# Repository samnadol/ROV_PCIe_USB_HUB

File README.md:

# PCIe USB Hub for Pi 5

# Images

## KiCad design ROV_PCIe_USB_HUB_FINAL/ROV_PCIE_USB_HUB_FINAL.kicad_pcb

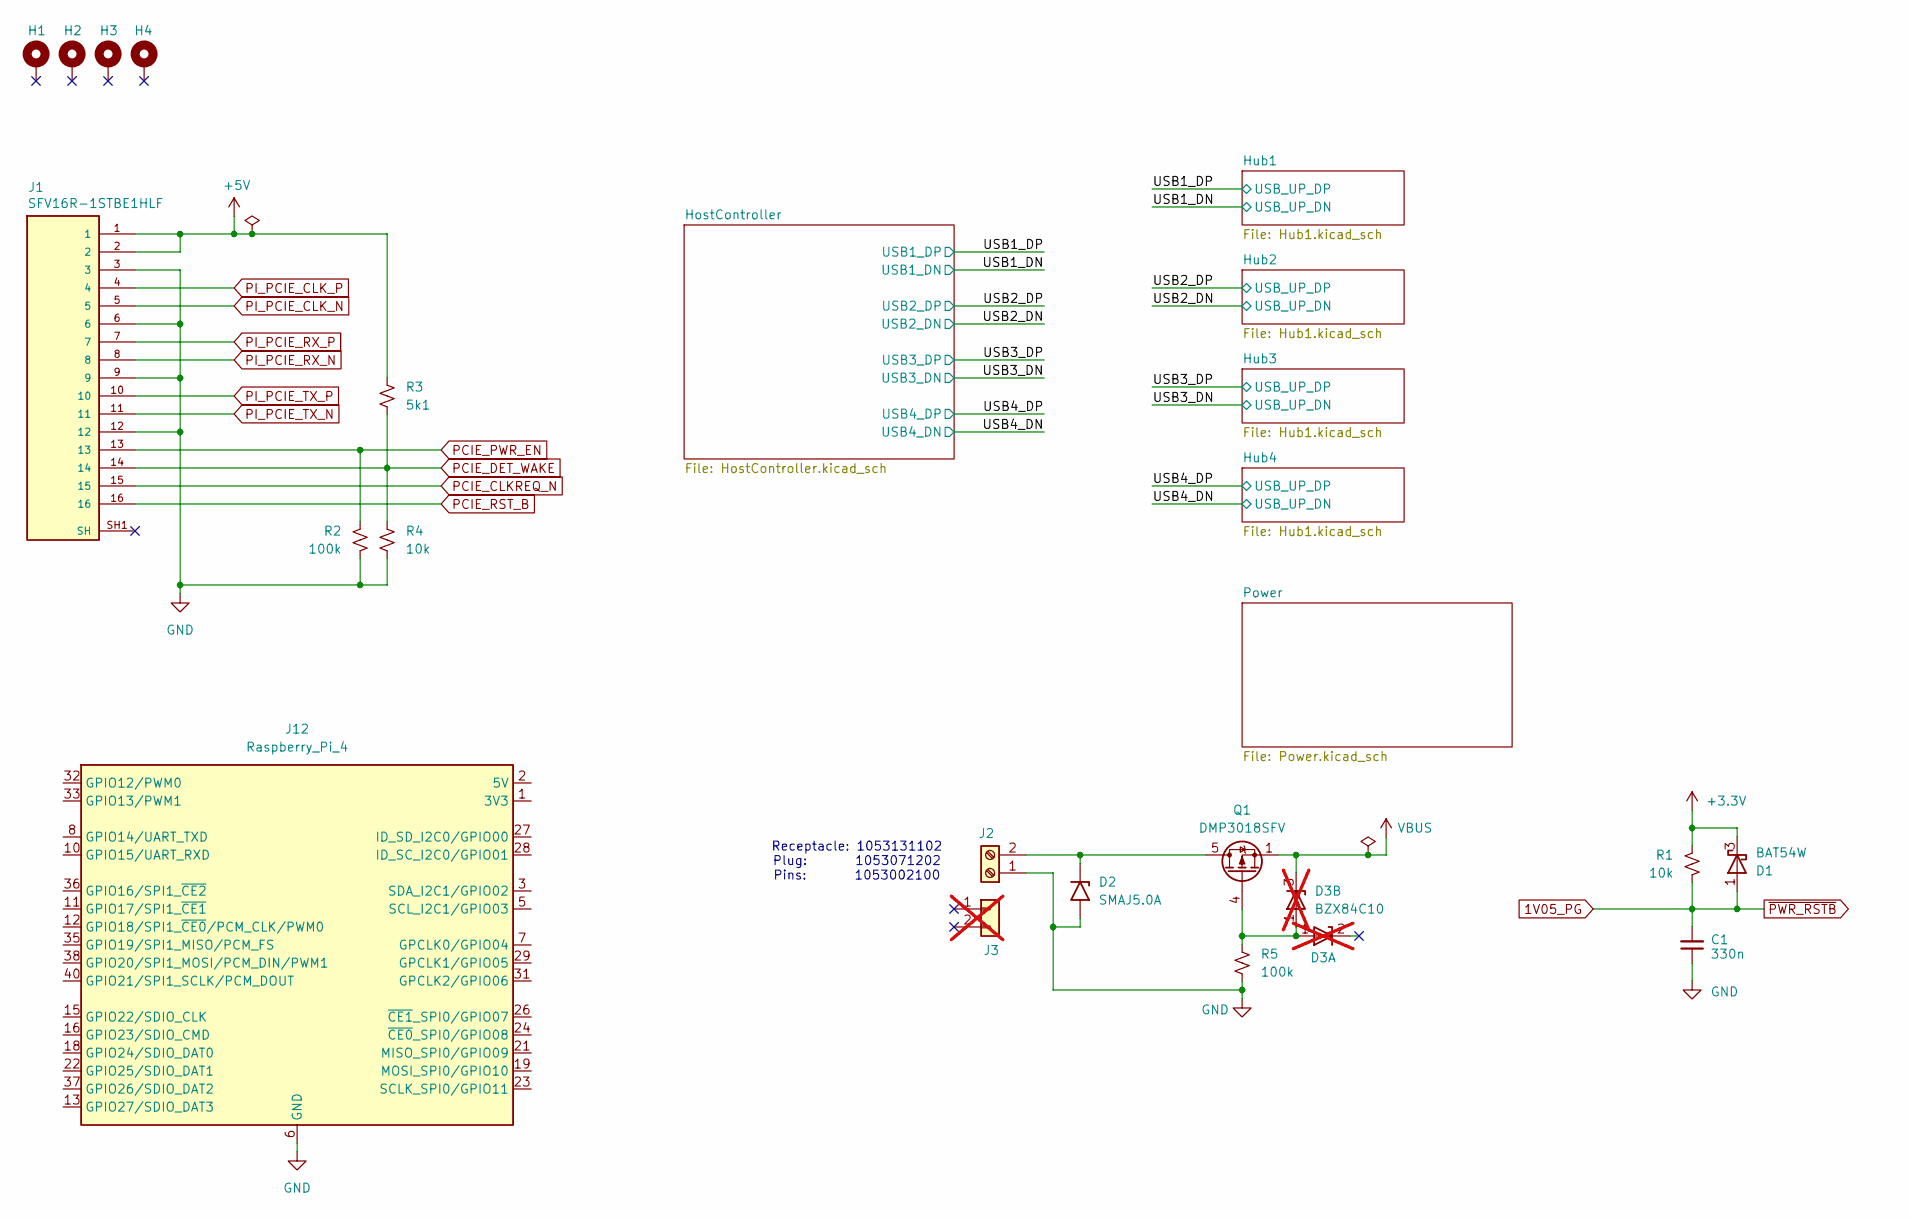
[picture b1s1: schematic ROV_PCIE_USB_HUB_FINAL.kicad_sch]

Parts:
C1: 330n; C_0402_1005Metric
D1: BAT54W; SOT-323_SC-70
D2: SMAJ5.0A; D_SMA; Part Number SMAJ5.0A
D3: BZX84C10; SOT-23; not fitted
H1, H2, H3, H4: MountingHole_Pad; MountingHole_2.7mm_M2.5_Pad
J1: SFV16R-1STBE1HLF; AMPHENOL_SFV16R-1STBE1HLF; PARTREV B
J2: 1053131102; Part Number 1053131102
J3: 1053071202; Part Number 1053071202; not fitted
J12: Raspberry_Pi_4; PinSocket_2x20_P2.54mm_Vertical
Q1: DMP3018SFV; Diodes_PowerDI3333-8; Part Number DMP3018SFV
R1, R4: 10k; R_0603_1608Metric
R2: 100k; R_0603_1608Metric
R3: 5k1; R_0603_1608Metric
R5: 100k; R_0603_1608Metric; Part Number RC0603FR-07100KL

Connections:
1V05_PG: C1.2, D1.1 (A), R1.2; also elsewhere on the board
+3.3V: D1.3 (K), R1.1; also elsewhere on the board
+5V: J1.1, J1.2, R3.1; also elsewhere on the board
GND: C1.1, D2.2 (A2), J1.3, J1.6, J1.9, J1.12, J2.1, J12.6 (GND), J12.9 (GND), J12.14 (GND), J12.20 (GND), J12.25 (GND), J12.30 (GND), J12.34 (GND), J12.39 (GND), R2.2, R4.2, R5.2; also elsewhere on the board
unnamed: D2.1 (A1), J2.2, Q1.5 (D)
unnamed: D3.1 (A), Q1.4 (G), R5.1
unnamed: J12.1 (3V3), J12.17 (3V3)
unnamed: J12.2 (5V), J12.4 (5V)
PCIE_CLKREQ_N: J1.15; also elsewhere on the board
PCIE_DET_WAKE: J1.14, R3.2, R4.1; also elsewhere on the board
PCIE_PWR_EN: J1.13, R2.1; also elsewhere on the board
PCIE_RST_B: J1.16; also elsewhere on the board
PI_PCIE_CLK_N: J1.5; also elsewhere on the board
PI_PCIE_CLK_P: J1.4; also elsewhere on the board
PI_PCIE_RX_N: J1.8; also elsewhere on the board
PI_PCIE_RX_P: J1.7; also elsewhere on the board
PI_PCIE_TX_N: J1.11; also elsewhere on the board
PI_PCIE_TX_P: J1.10; also elsewhere on the board
VBUS: D3.3 (K), Q1.1 (S), Q1.2 (S), Q1.3 (S); also elsewhere on the board

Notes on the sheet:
Receptacle: 1053131102 Plug: 1053071202 Pins: 1053002100

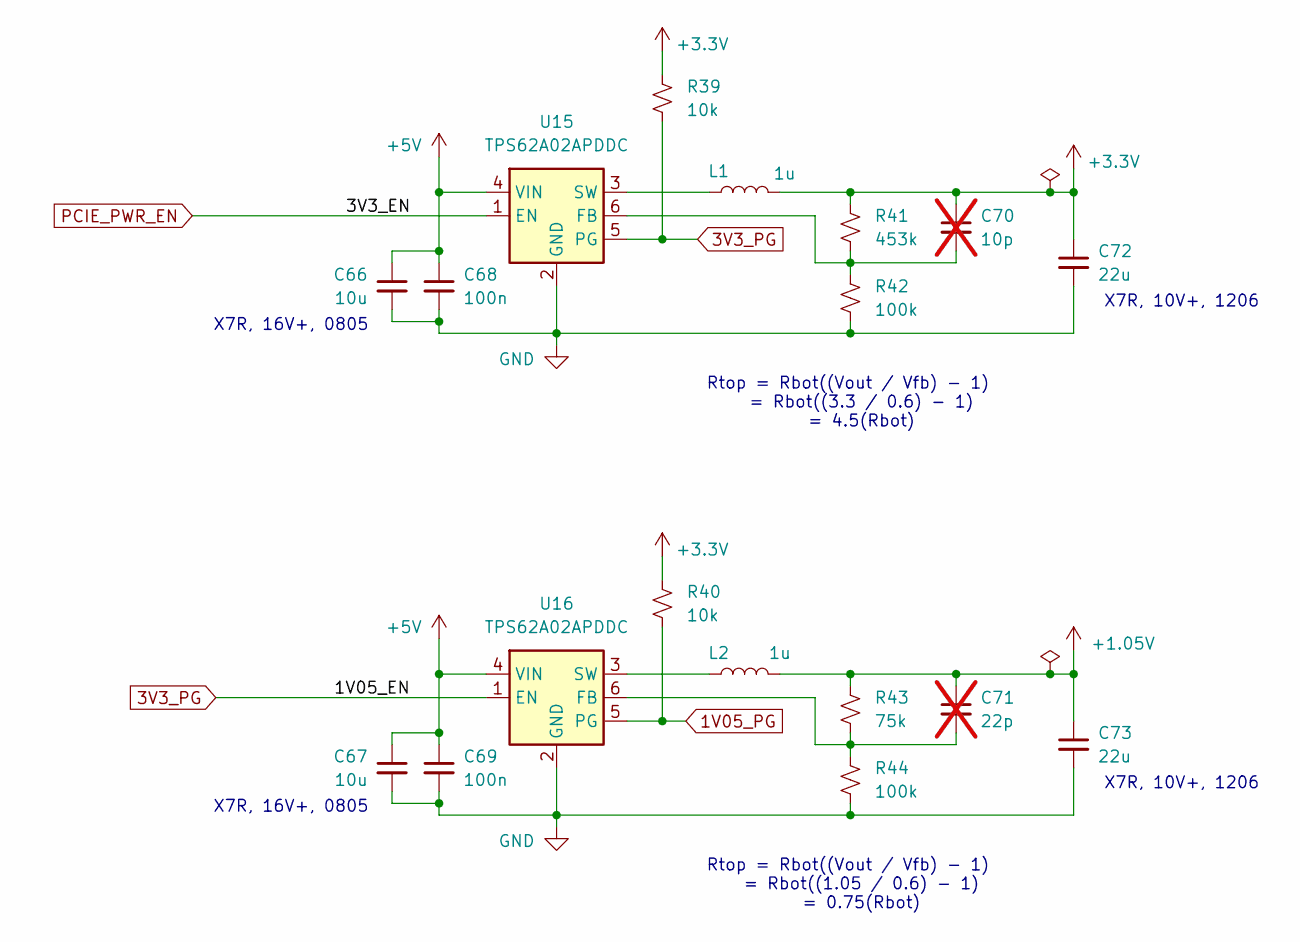
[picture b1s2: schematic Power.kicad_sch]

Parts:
C66, C67: 10u; C_0805_2012Metric; Part Number CC0805KRX5R8BB106
C68, C69: 100n; C_0402_1005Metric; Part Number CC0402KRX7R8BB104
C70: 10p; C_0402_1005Metric; Part Number CL05C100JB5NNNC; not fitted
C71: 22p; C_0402_1005Metric; Part Number CL05C220JB5NNNC; not fitted
C72, C73: 22u; C_1206_3216Metric; Part Number CC1206KKX5R8BB226
L1, L2: 1u; L_1008_2520Metric; Part Number DFE252012F-1R0M
R39, R40: 10k; R_0603_1608Metric; Part Number RC0603FR-0710KL
R41: 453k; R_0603_1608Metric; Part Number RC0603FR-07453KL
R42, R44: 100k; R_0603_1608Metric; Part Number RC0603FR-07100KL
R43: 75k; R_0603_1608Metric; Part Number RC0603FR-0775KL
U15, U16: TPS62A02APDDC; SOT-23-6; Part Number TPS62A02APDDC

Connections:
1V05_PG: R40.2, U16.5 (PG); also elsewhere on the board
3V3_PG: R39.2, U15.5 (PG), U16.1 (EN)
+1.05V: C71.1, C73.1, L2.2, R43.1; also elsewhere on the board
+3.3V: C70.1, C72.1, L1.2, R39.1, R40.1, R41.1; also elsewhere on the board
+5V: C66.1, C67.1, C68.1, C69.1, U15.4 (VIN), U16.4 (VIN); also elsewhere on the board
GND: C66.2, C67.2, C68.2, C69.2, C72.2, C73.2, R42.2, R44.2, U15.2 (GND), U16.2 (GND); also elsewhere on the board
unnamed: C70.2, R41.2, R42.1, U15.6 (FB)
unnamed: L1.1, U15.3 (SW)
unnamed: C71.2, R43.2, R44.1, U16.6 (FB)
unnamed: L2.1, U16.3 (SW)
PCIE_PWR_EN: U15.1 (EN); also elsewhere on the board

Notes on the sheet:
X7R, 10V+, 1206
Rtop = Rbot((Vout / Vfb) - 1) = Rbot((1.05 / 0.6) - 1) = 0.75(Rbot)
Rtop = Rbot((Vout / Vfb) - 1) = Rbot((3.3 / 0.6) - 1) = 4.5(Rbot)
X7R, 16V+, 0805

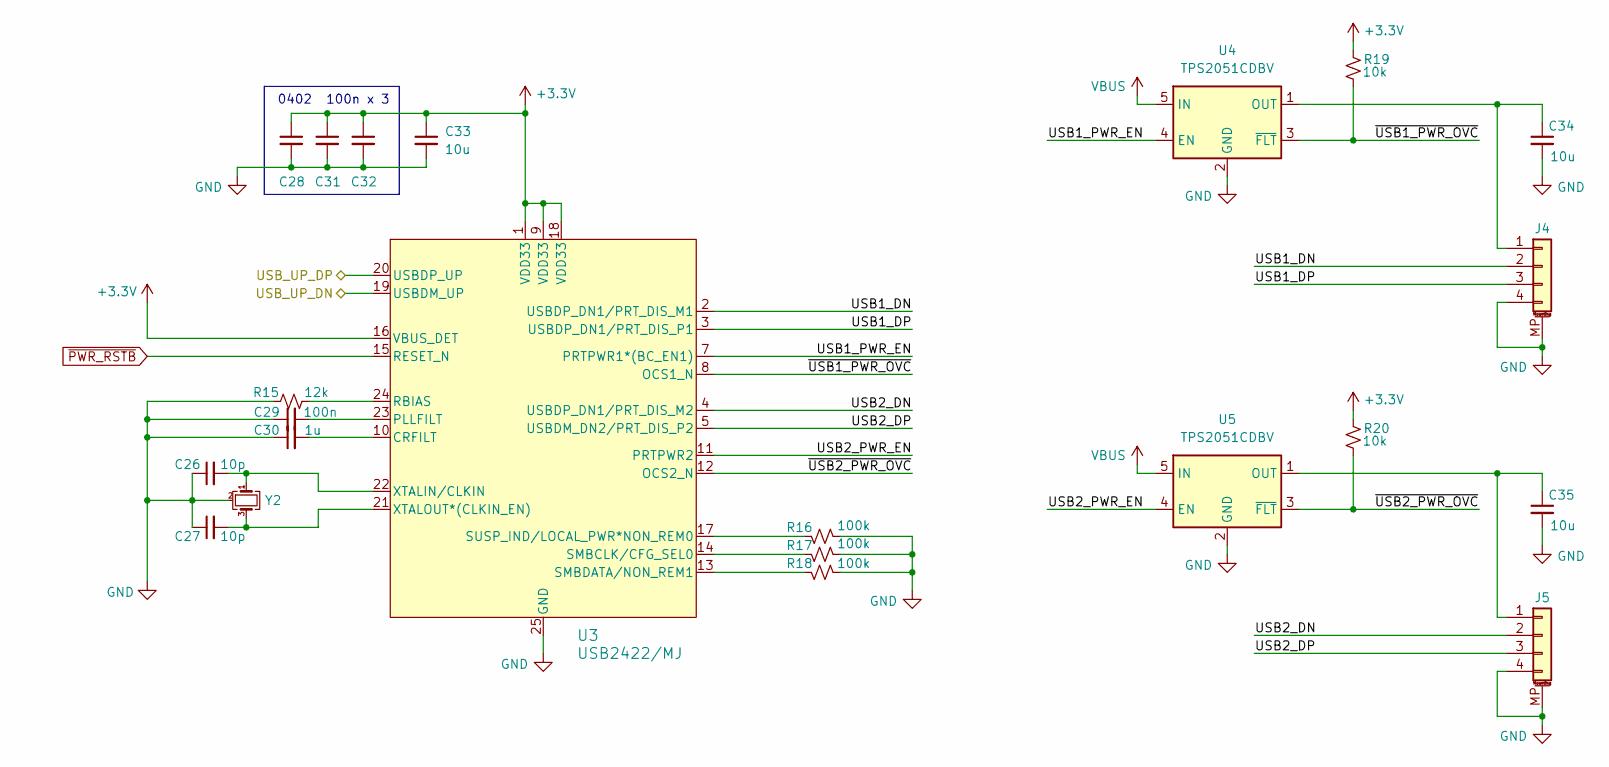
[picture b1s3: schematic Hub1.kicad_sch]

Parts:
C26, C27: 10p; C_0402_1005Metric
C28, C29, C31, C32: 100n; C_0402_1005Metric
C30: 1u; C_0603_1608Metric
C33: 10u; C_0805_2012Metric
C34, C35: 10u; C_0805_2012Metric; Part Number CC0805KRX5R8BB106
J4, J5: SM04B-SRSS-TB; JST_SH_SM04B-SRSS-TB_1x04-1MP_P1.00mm_Horizontal
R15: 12k; R_0603_1608Metric
R16, R17, R18: 100k; R_0603_1608Metric
R19, R20: 10k; R_0402_1005Metric
U3: USB2422/MJ; QFN-24-1EP_4x4mm_P0.5mm_EP2.5x2.5mm_ThermalVias
U4, U5: TPS2051CDBV; SOT-23-5
Y2: ECS-240-8-37B-CKY-TR; Crystal_SMD_2016-4Pin_2.0x1.6mm

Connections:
1V05_PG: U3.15 (RESET_N); also elsewhere on the board
+3.3V: C28.1, C31.1, C32.1, C33.1, R19.1, R20.1, U3.1 (VDD33), U3.9 (VDD33), U3.16 (VBUS_DET), U3.18 (VDD33); also elsewhere on the board
/Hub1/USB1_DN: J4.2, U3.2 (USBDP_DN1/PRT_DIS_M1)
/Hub1/USB1_DP: J4.3, U3.3 (USBDP_DN1/PRT_DIS_P1)
/Hub1/USB1_PWR_EN: U3.7 (PRTPWR1*(BC_EN1)), U4.4 (EN)
/Hub1/USB2_DN: J5.2, U3.4 (USBDP_DN1/PRT_DIS_M2)
/Hub1/USB2_DP: J5.3, U3.5 (USBDM_DN2/PRT_DIS_P2)
/Hub1/USB2_PWR_EN: U3.11 (PRTPWR2), U5.4 (EN)
/Hub1/~USB1_PWR_OVC: R19.2, U3.8 (OCS1_N), U4.3 (~FLT)
/Hub1/~USB2_PWR_OVC: R20.2, U3.12 (OCS2_N), U5.3 (~FLT)
/USB1_DN: U3.19 (USBDM_UP); also elsewhere on the board
/USB1_DP: U3.20 (USBDP_UP); also elsewhere on the board
GND: C26.1, C27.1, C28.2, C29.1, C30.1, C31.2, C32.2, C33.2, C34.2, C35.2, J4.4, J4.MP (MountPin), J5.4, J5.MP (MountPin), R15.1, R16.2, R17.2, R18.2, U3.25 (GND), U4.2 (GND), U5.2 (GND), Y2.2 (G), Y2.4 (G); also elsewhere on the board
unnamed: C34.1, J4.1, U4.1 (OUT)
unnamed: C35.1, J5.1, U5.1 (OUT)
unnamed: C30.2, U3.10 (CRFILT)
unnamed: C29.2, U3.23 (PLLFILT)
unnamed: R15.2, U3.24 (RBIAS)
unnamed: R17.1, U3.14 (SMBCLK/CFG_SEL0)
unnamed: R18.1, U3.13 (SMBDATA/NON_REM1)
unnamed: R16.1, U3.17 (SUSP_IND/LOCAL_PWR*NON_REM0)
unnamed: C26.2, U3.22 (XTALIN/CLKIN), Y2.1
unnamed: C27.2, U3.21 (XTALOUT*(CLKIN_EN)), Y2.3
VBUS: U4.5 (IN), U5.5 (IN); also elsewhere on the board

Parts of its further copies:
C36, C37, C46, C47, C56, C57: 10p; C_0402_1005Metric
C38, C39, C41, C42, C48, C49, C51, C52, C58, C59, C61, C62: 100n; C_0402_1005Metric
C40, C50, C60: 1u; C_0603_1608Metric
C43, C53, C63: 10u; C_0805_2012Metric
C44, C45, C54, C55, C64, C65: 10u; C_0805_2012Metric; Part Number CC0805KRX5R8BB106
J6, J7, J8, J9, J10, J11: SM04B-SRSS-TB; JST_SH_SM04B-SRSS-TB_1x04-1MP_P1.00mm_Horizontal
R21, R27, R33: 12k; R_0603_1608Metric
R22, R23, R24, R28, R29, R30, R34, R35, R36: 100k; R_0603_1608Metric
R25, R26, R31, R32, R37, R38: 10k; R_0402_1005Metric
U6, U9, U12: USB2422/MJ; QFN-24-1EP_4x4mm_P0.5mm_EP2.5x2.5mm_ThermalVias
U7, U8, U10, U11, U13, U14: TPS2051CDBV; SOT-23-5
Y3, Y4, Y5: ECS-240-8-37B-CKY-TR; Crystal_SMD_2016-4Pin_2.0x1.6mm

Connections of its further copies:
1V05_PG: U6.15 (RESET_N), U9.15 (RESET_N), U12.15 (RESET_N); also elsewhere on the board
+3.3V: C38.1, C41.1, C42.1, C43.1, C48.1, C51.1, C52.1, C53.1, C58.1, C61.1, C62.1, C63.1, R25.1, R26.1, R31.1, R32.1, R37.1, R38.1, U6.1 (VDD33), U6.9 (VDD33), U6.16 (VBUS_DET), U6.18 (VDD33), U9.1 (VDD33), U9.9 (VDD33), U9.16 (VBUS_DET), U9.18 (VDD33), U12.1 (VDD33), U12.9 (VDD33), U12.16 (VBUS_DET), U12.18 (VDD33); also elsewhere on the board
/Hub2/USB1_DN: J6.2, U6.2 (USBDP_DN1/PRT_DIS_M1)
/Hub2/USB1_DP: J6.3, U6.3 (USBDP_DN1/PRT_DIS_P1)
/Hub2/USB1_PWR_EN: U6.7 (PRTPWR1*(BC_EN1)), U7.4 (EN)
/Hub2/USB2_DN: J7.2, U6.4 (USBDP_DN1/PRT_DIS_M2)
/Hub2/USB2_DP: J7.3, U6.5 (USBDM_DN2/PRT_DIS_P2)
/Hub2/USB2_PWR_EN: U6.11 (PRTPWR2), U8.4 (EN)
/Hub2/~USB1_PWR_OVC: R25.2, U6.8 (OCS1_N), U7.3 (~FLT)
/Hub2/~USB2_PWR_OVC: R26.2, U6.12 (OCS2_N), U8.3 (~FLT)
/Hub3/USB1_DN: J8.2, U9.2 (USBDP_DN1/PRT_DIS_M1)
/Hub3/USB1_DP: J8.3, U9.3 (USBDP_DN1/PRT_DIS_P1)
/Hub3/USB1_PWR_EN: U9.7 (PRTPWR1*(BC_EN1)), U10.4 (EN)
/Hub3/USB2_DN: J9.2, U9.4 (USBDP_DN1/PRT_DIS_M2)
/Hub3/USB2_DP: J9.3, U9.5 (USBDM_DN2/PRT_DIS_P2)
/Hub3/USB2_PWR_EN: U9.11 (PRTPWR2), U11.4 (EN)
/Hub3/~USB1_PWR_OVC: R31.2, U9.8 (OCS1_N), U10.3 (~FLT)
/Hub3/~USB2_PWR_OVC: R32.2, U9.12 (OCS2_N), U11.3 (~FLT)
/Hub4/USB1_DN: J10.2, U12.2 (USBDP_DN1/PRT_DIS_M1)
/Hub4/USB1_DP: J10.3, U12.3 (USBDP_DN1/PRT_DIS_P1)
/Hub4/USB1_PWR_EN: U12.7 (PRTPWR1*(BC_EN1)), U13.4 (EN)
/Hub4/USB2_DN: J11.2, U12.4 (USBDP_DN1/PRT_DIS_M2)
/Hub4/USB2_DP: J11.3, U12.5 (USBDM_DN2/PRT_DIS_P2)
/Hub4/USB2_PWR_EN: U12.11 (PRTPWR2), U14.4 (EN)
/Hub4/~USB1_PWR_OVC: R37.2, U12.8 (OCS1_N), U13.3 (~FLT)
/Hub4/~USB2_PWR_OVC: R38.2, U12.12 (OCS2_N), U14.3 (~FLT)
/USB2_DN: U6.19 (USBDM_UP); also elsewhere on the board
/USB2_DP: U6.20 (USBDP_UP); also elsewhere on the board
/USB3_DN: U9.19 (USBDM_UP); also elsewhere on the board
/USB3_DP: U9.20 (USBDP_UP); also elsewhere on the board
/USB4_DN: U12.19 (USBDM_UP); also elsewhere on the board
/USB4_DP: U12.20 (USBDP_UP); also elsewhere on the board
GND: C36.1, C37.1, C38.2, C39.1, C40.1, C41.2, C42.2, C43.2, C44.2, C45.2, C46.1, C47.1, C48.2, C49.1, C50.1, C51.2, C52.2, C53.2, C54.2, C55.2, C56.1, C57.1, C58.2, C59.1, C60.1, C61.2, C62.2, C63.2, C64.2, C65.2, J6.4, J6.MP (MountPin), J7.4, J7.MP (MountPin), J8.4, J8.MP (MountPin), J9.4, J9.MP (MountPin), J10.4, J10.MP (MountPin), J11.4, J11.MP (MountPin), R21.1, R22.2, R23.2, R24.2, R27.1, R28.2, R29.2, R30.2, R33.1, R34.2, R35.2, R36.2, U6.25 (GND), U7.2 (GND), U8.2 (GND), U9.25 (GND), U10.2 (GND), U11.2 (GND), U12.25 (GND), U13.2 (GND), U14.2 (GND), Y3.2 (G), Y3.4 (G), Y4.2 (G), Y4.4 (G), Y5.2 (G), Y5.4 (G); also elsewhere on the board
unnamed: C44.1, J6.1, U7.1 (OUT)
unnamed: C45.1, J7.1, U8.1 (OUT)
unnamed: C54.1, J8.1, U10.1 (OUT)
unnamed: C55.1, J9.1, U11.1 (OUT)
unnamed: C64.1, J10.1, U13.1 (OUT)
unnamed: C65.1, J11.1, U14.1 (OUT)
unnamed: C40.2, U6.10 (CRFILT)
unnamed: C39.2, U6.23 (PLLFILT)
unnamed: R21.2, U6.24 (RBIAS)
unnamed: R23.1, U6.14 (SMBCLK/CFG_SEL0)
unnamed: R24.1, U6.13 (SMBDATA/NON_REM1)
unnamed: R22.1, U6.17 (SUSP_IND/LOCAL_PWR*NON_REM0)
unnamed: C36.2, U6.22 (XTALIN/CLKIN), Y3.1
unnamed: C37.2, U6.21 (XTALOUT*(CLKIN_EN)), Y3.3
unnamed: C50.2, U9.10 (CRFILT)
unnamed: C49.2, U9.23 (PLLFILT)
unnamed: R27.2, U9.24 (RBIAS)
unnamed: R29.1, U9.14 (SMBCLK/CFG_SEL0)
unnamed: R30.1, U9.13 (SMBDATA/NON_REM1)
unnamed: R28.1, U9.17 (SUSP_IND/LOCAL_PWR*NON_REM0)
unnamed: C46.2, U9.22 (XTALIN/CLKIN), Y4.1
unnamed: C47.2, U9.21 (XTALOUT*(CLKIN_EN)), Y4.3
unnamed: C60.2, U12.10 (CRFILT)
unnamed: C59.2, U12.23 (PLLFILT)
unnamed: R33.2, U12.24 (RBIAS)
unnamed: R35.1, U12.14 (SMBCLK/CFG_SEL0)
unnamed: R36.1, U12.13 (SMBDATA/NON_REM1)
unnamed: R34.1, U12.17 (SUSP_IND/LOCAL_PWR*NON_REM0)
unnamed: C56.2, U12.22 (XTALIN/CLKIN), Y5.1
unnamed: C57.2, U12.21 (XTALOUT*(CLKIN_EN)), Y5.3
VBUS: U7.5 (IN), U8.5 (IN), U10.5 (IN), U11.5 (IN), U13.5 (IN), U14.5 (IN); also elsewhere on the board

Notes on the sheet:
0402
100n x 3

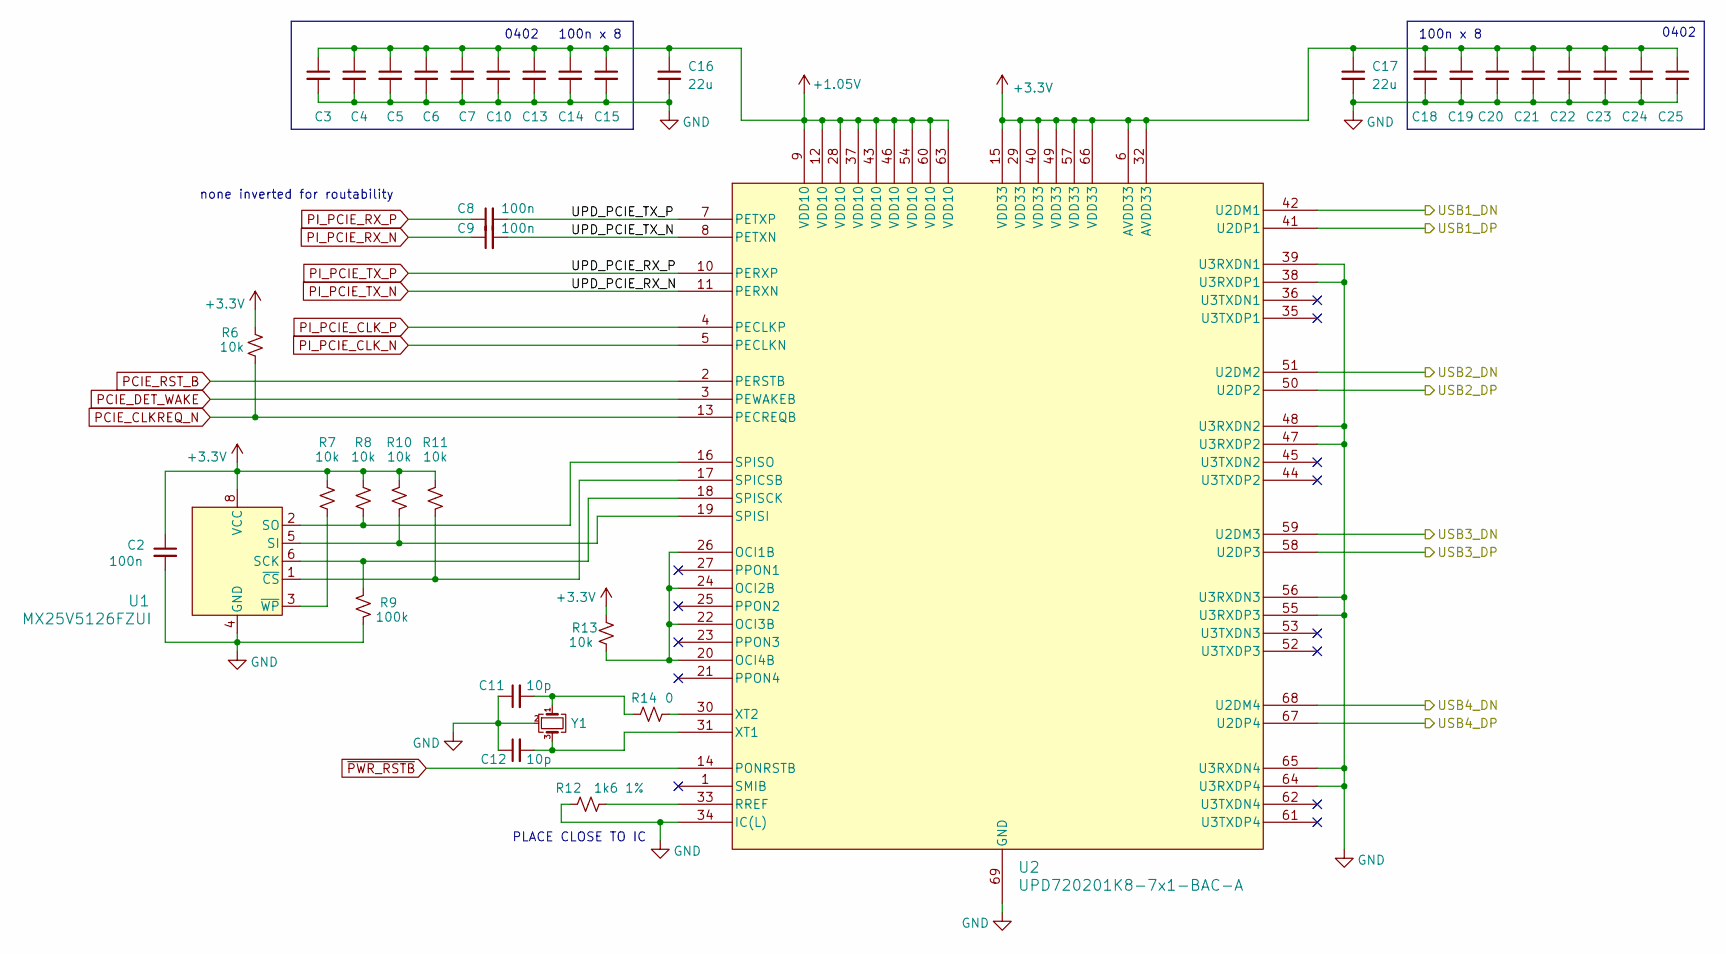
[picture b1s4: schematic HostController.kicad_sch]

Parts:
C2, C3, C4, C5, C6, C7, C8, C9, C10, C13, C14, C15, C18, C19, C20, C21, C22, C23, C24, C25: 100n; C_0402_1005Metric
C11, C12: 10p; C_0402_1005Metric
C16, C17: 22u; C_1206_3216Metric
R6, R7, R8, R10, R11, R13: 10k; R_0402_1005Metric
R9: 100k; R_0603_1608Metric
R12: 1k6 1%; R_0603_1608Metric
R14: 0; R_0402_1005Metric
U1: MX25V5126FZUI; Winbond_USON-8-1EP_3x2mm_P0.5mm_EP0.2x1.6mm
U2: UPD720201K8-7x1-BAC-A; QFN-68-1EP_8x8mm_P0.4mm_EP6.2x6.2mm
Y1: ECS-240-8-37B-CKY-TR; Crystal_SMD_2016-4Pin_2.0x1.6mm

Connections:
1V05_PG: U2.14 (PONRSTB); also elsewhere on the board
+1.05V: C3.1, C4.1, C5.1, C6.1, C7.1, C10.1, C13.1, C14.1, C15.1, C16.1, U2.9 (VDD10), U2.12 (VDD10), U2.28 (VDD10), U2.37 (VDD10), U2.43 (VDD10), U2.46 (VDD10), U2.54 (VDD10), U2.60 (VDD10), U2.63 (VDD10); also elsewhere on the board
+3.3V: C2.1, C17.1, C18.1, C19.1, C20.1, C21.1, C22.1, C23.1, C24.1, C25.1, R6.1, R7.1, R8.1, R10.1, R11.1, R13.1, U1.8 (VCC), U2.6 (AVDD33), U2.15 (VDD33), U2.29 (VDD33), U2.32 (AVDD33), U2.40 (VDD33), U2.49 (VDD33), U2.57 (VDD33), U2.66 (VDD33); also elsewhere on the board
/HostController/UPD_PCIE_TX_N: C9.2, U2.8 (PETXN)
/HostController/UPD_PCIE_TX_P: C8.2, U2.7 (PETXP)
/USB1_DN: U2.42 (U2DM1); also elsewhere on the board
/USB1_DP: U2.41 (U2DP1); also elsewhere on the board
/USB2_DN: U2.51 (U2DM2); also elsewhere on the board
/USB2_DP: U2.50 (U2DP2); also elsewhere on the board
/USB3_DN: U2.59 (U2DM3); also elsewhere on the board
/USB3_DP: U2.58 (U2DP3); also elsewhere on the board
/USB4_DN: U2.68 (U2DM4); also elsewhere on the board
/USB4_DP: U2.67 (U2DP4); also elsewhere on the board
GND: C2.2, C3.2, C4.2, C5.2, C6.2, C7.2, C10.2, C11.1, C12.1, C13.2, C14.2, C15.2, C16.2, C17.2, C18.2, C19.2, C20.2, C21.2, C22.2, C23.2, C24.2, C25.2, R9.2, R12.1, U1.4 (GND), U1.9 (EP), U2.34 (IC(L)), U2.38 (U3RXDP1), U2.39 (U3RXDN1), U2.47 (U3RXDP2), U2.48 (U3RXDN2), U2.55 (U3RXDP3), U2.56 (U3RXDN3), U2.64 (U3RXDP4), U2.65 (U3RXDN4), U2.69 (GND), Y1.2 (G), Y1.4 (G); also elsewhere on the board
unnamed: C11.2, R14.1, Y1.1
unnamed: R9.1, U1.6 (SCK), U2.18 (SPISCK)
unnamed: R10.2, U1.5 (SI), U2.19 (SPISI)
unnamed: R8.2, U1.2 (SO), U2.16 (SPISO)
unnamed: R11.2, U1.1 (~CS), U2.17 (SPICSB)
unnamed: R7.2, U1.3 (~WP)
unnamed: R13.2, U2.20 (OCI4B), U2.22 (OCI3B), U2.24 (OCI2B), U2.26 (OCI1B)
unnamed: R12.2, U2.33 (RREF)
unnamed: C12.2, U2.31 (XT1), Y1.3
unnamed: R14.2, U2.30 (XT2)
PCIE_CLKREQ_N: R6.2, U2.13 (PECREQB); also elsewhere on the board
PCIE_DET_WAKE: U2.3 (PEWAKEB); also elsewhere on the board
PCIE_RST_B: U2.2 (PERSTB); also elsewhere on the board
PI_PCIE_CLK_N: U2.5 (PECLKN); also elsewhere on the board
PI_PCIE_CLK_P: U2.4 (PECLKP); also elsewhere on the board
PI_PCIE_RX_N: C9.1; also elsewhere on the board
PI_PCIE_RX_P: C8.1; also elsewhere on the board
PI_PCIE_TX_N: U2.11 (PERXN); also elsewhere on the board
PI_PCIE_TX_P: U2.10 (PERXP); also elsewhere on the board

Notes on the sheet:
100n x 8
0402
none inverted for routability
PLACE CLOSE TO IC

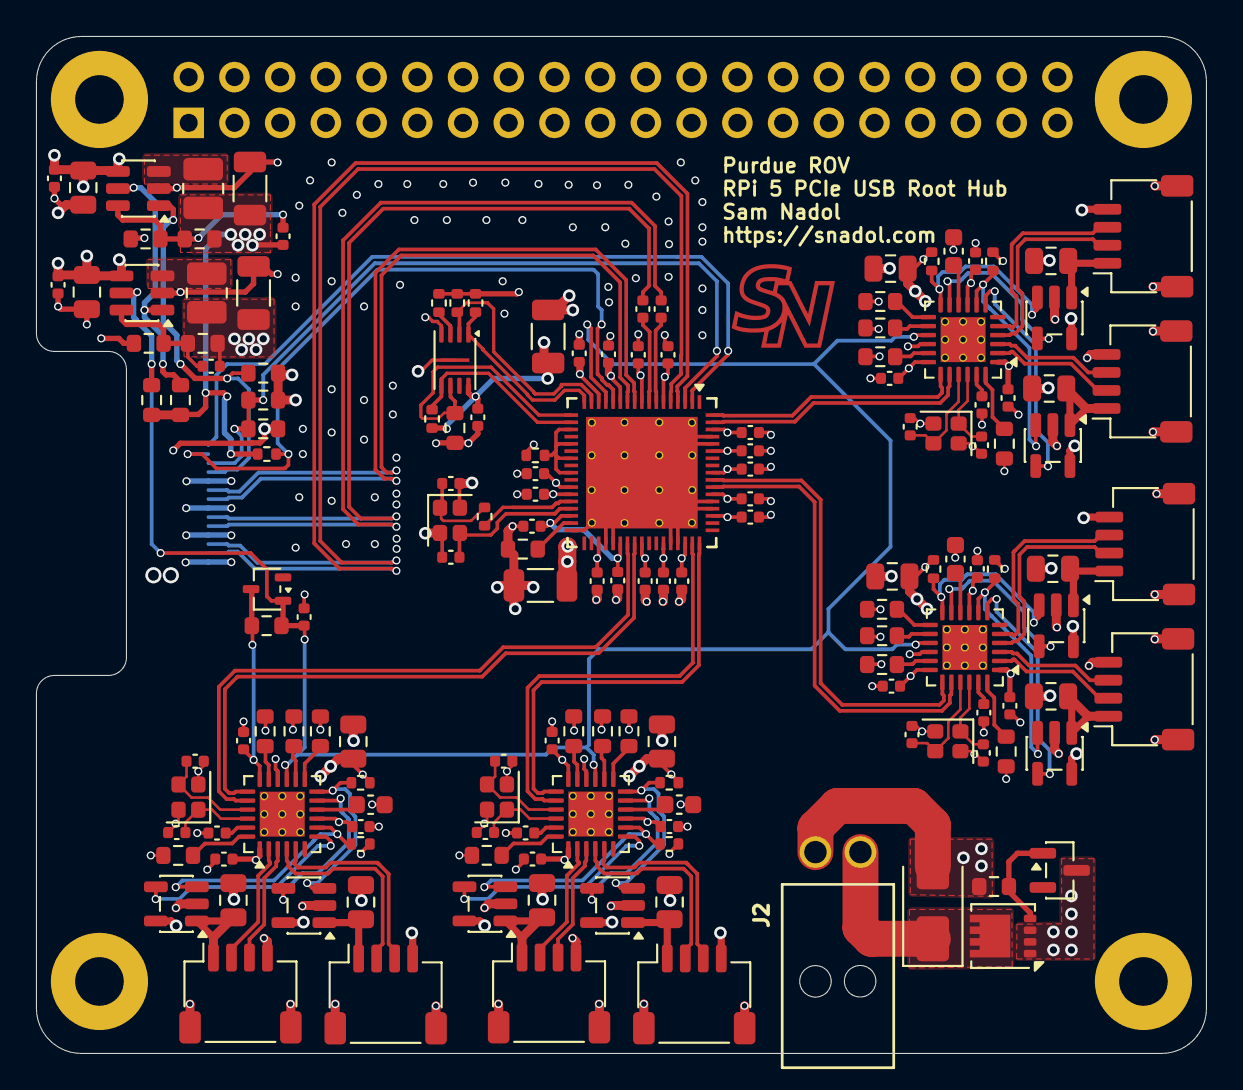
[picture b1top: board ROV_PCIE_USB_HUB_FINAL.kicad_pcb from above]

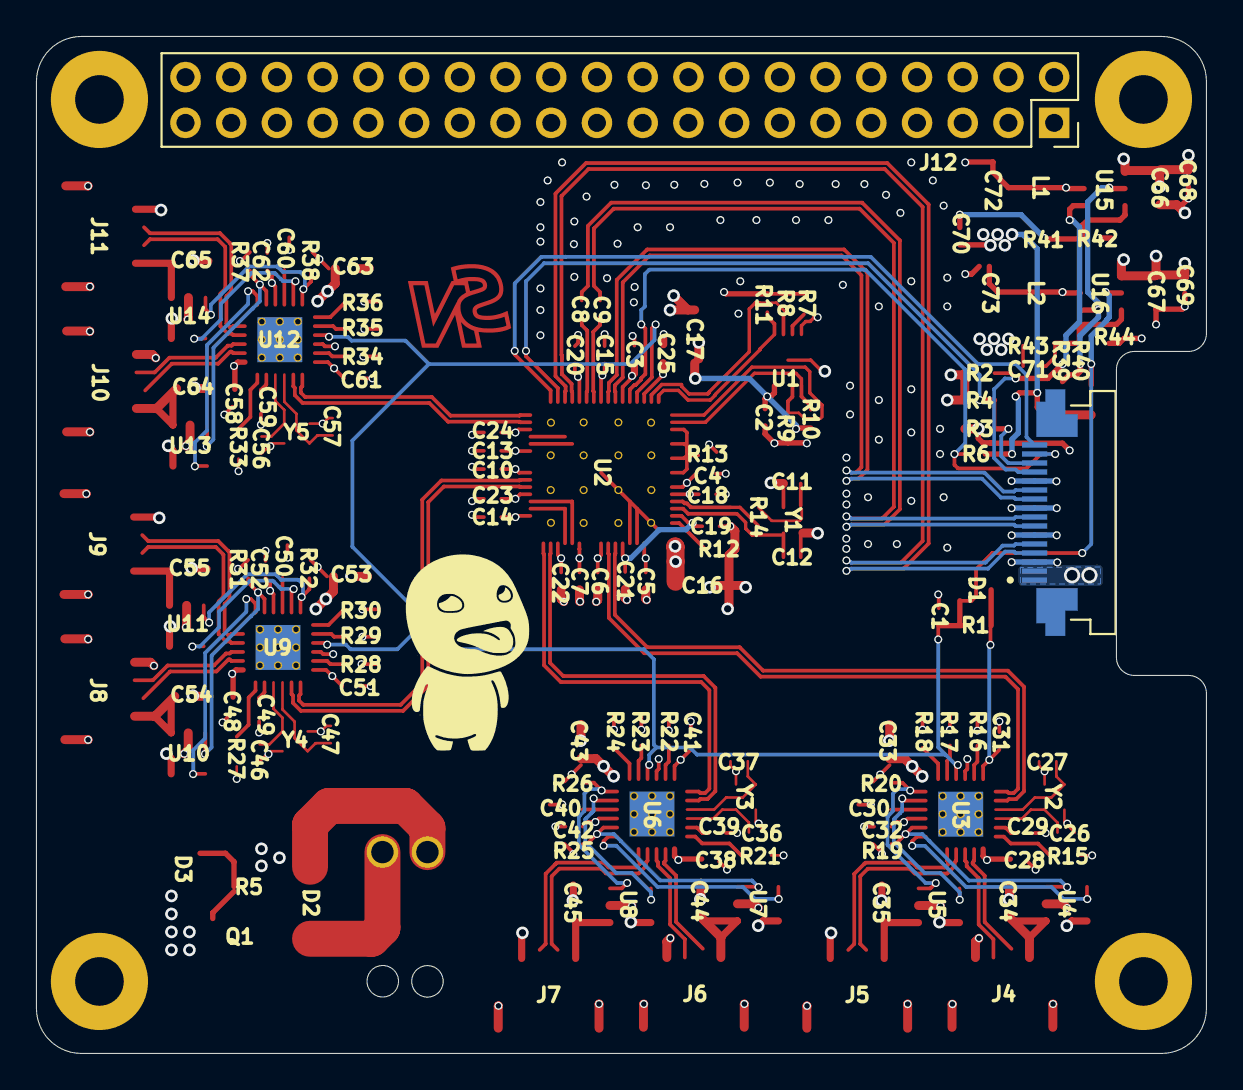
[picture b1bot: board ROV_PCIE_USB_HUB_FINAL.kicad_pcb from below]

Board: 4 copper layers, 65.0 x 56.5 mm, 159 parts (2 on the bottom side), 117 nets.

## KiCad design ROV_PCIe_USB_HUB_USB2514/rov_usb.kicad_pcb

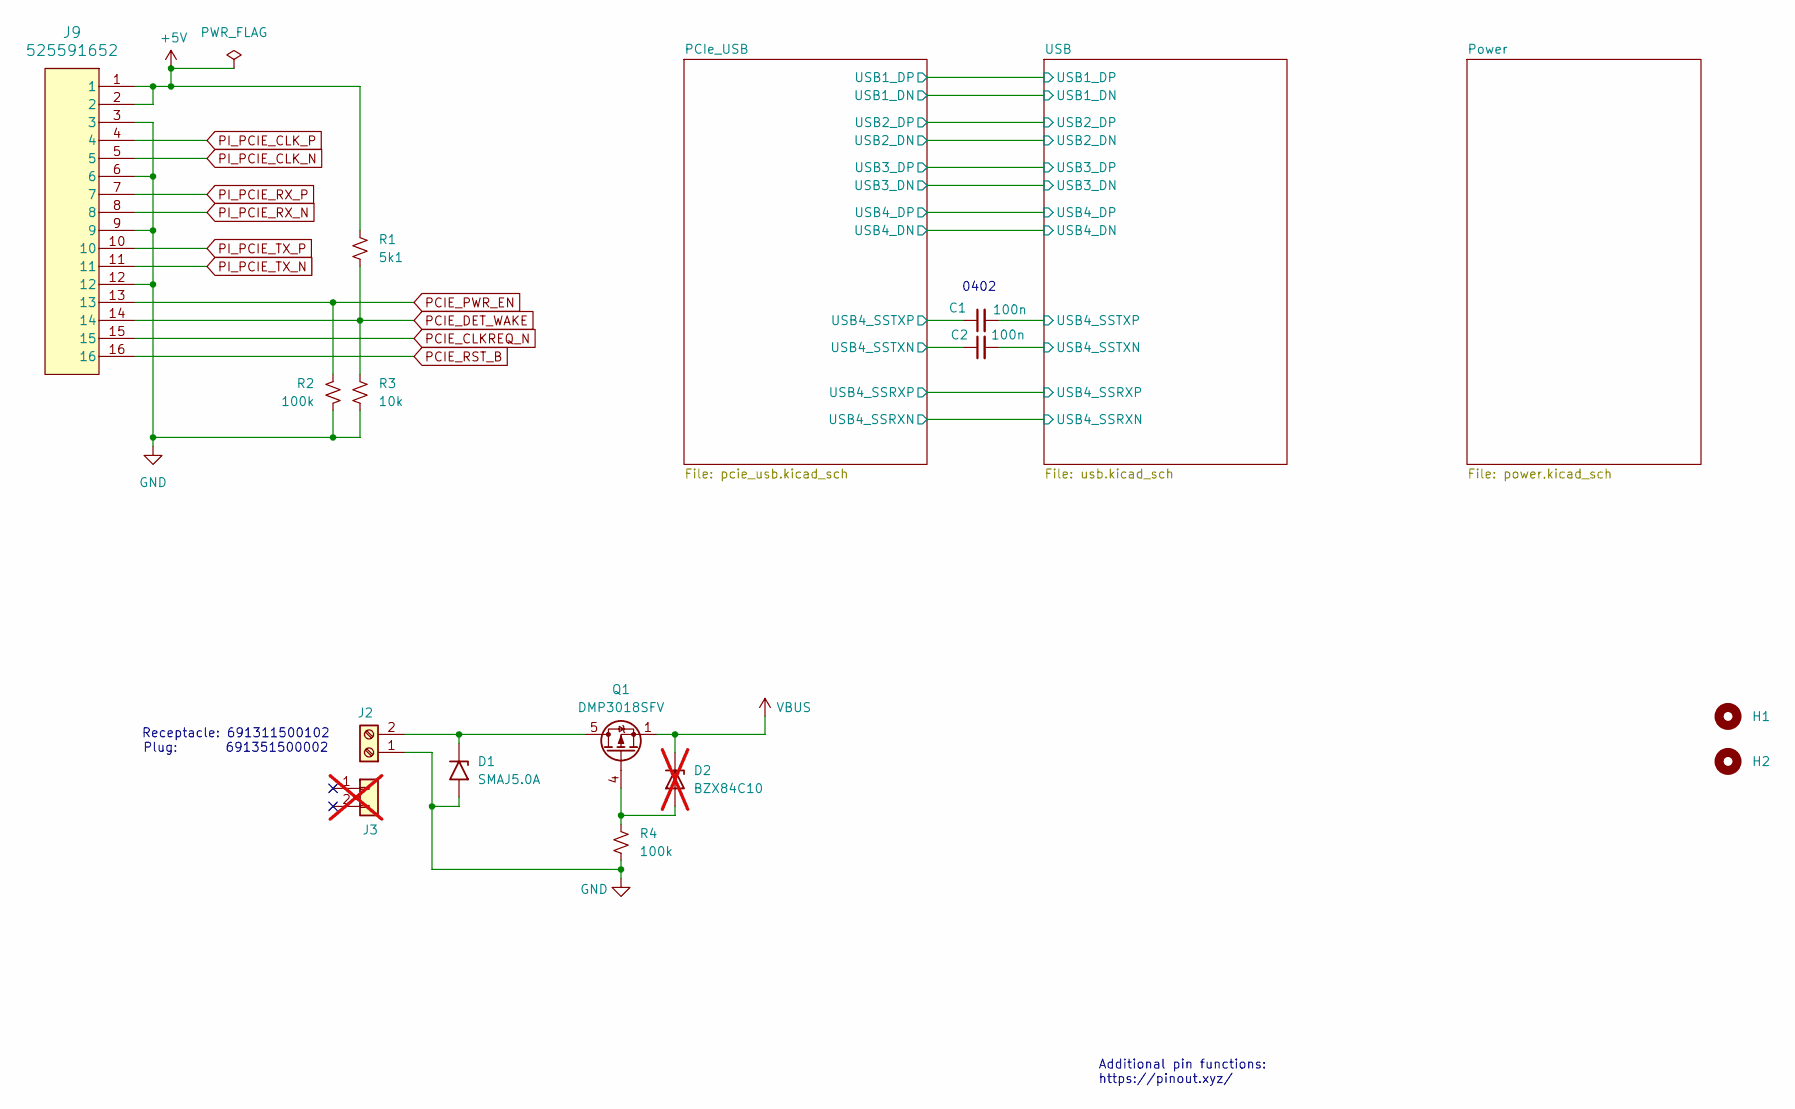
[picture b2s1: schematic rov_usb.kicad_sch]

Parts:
C1, C2: 100n; C_0402_1005Metric; Part Number CC0402KRX7R8BB104
D1: SMAJ5.0A; D_SMA; Part Number SMAJ5.0A
D2: BZX84C10; D_0402_1005Metric; not fitted
H1, H2: MountingHole; MountingHole_3.2mm_M3
J2: 691311500102; J_Wurth_WR-TBL_691311500102; Part Number 691311500102
J3: 691351500002; Part Number 691351500002; not fitted
J9: 525591652
Q1: DMP3018SFV; Diodes_PowerDI3333-8; Part Number DMP3018SFV
R1: 5k1; R_0603_1608Metric; Part Number RC0603FR-075K1L
R2, R4: 100k; R_0603_1608Metric; Part Number RC0603FR-07100KL
R3: 10k; R_0603_1608Metric; Part Number RC0603FR-0710KL

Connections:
+5V: J9.1, J9.2, R1.1; also elsewhere on the board
/PCIe_USB/USB4_SSTXN: C2.1; also elsewhere on the board
/PCIe_USB/USB4_SSTXP: C1.1; also elsewhere on the board
/USB/USB4_SSTXN: C2.2; also elsewhere on the board
/USB/USB4_SSTXP: C1.2; also elsewhere on the board
GND: D1.2 (A2), J2.1, J9.3, J9.6, J9.9, J9.12, R2.2, R3.2, R4.2; also elsewhere on the board
unnamed: D1.1 (A1), J2.2, Q1.5 (D)
unnamed: D2.2 (A), Q1.4 (G), R4.1
PCIE_CLKREQ_N: J9.15; also elsewhere on the board
PCIE_DET_WAKE: J9.14, R1.2, R3.1; also elsewhere on the board
PCIE_PWR_EN: J9.13, R2.1; also elsewhere on the board
PCIE_RST_B: J9.16; also elsewhere on the board
PI_PCIE_CLK_N: J9.5; also elsewhere on the board
PI_PCIE_CLK_P: J9.4; also elsewhere on the board
PI_PCIE_RX_N: J9.8; also elsewhere on the board
PI_PCIE_RX_P: J9.7; also elsewhere on the board
PI_PCIE_TX_N: J9.11; also elsewhere on the board
PI_PCIE_TX_P: J9.10; also elsewhere on the board
VBUS: D2.1 (K), Q1.1 (S), Q1.2 (S), Q1.3 (S); also elsewhere on the board

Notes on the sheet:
Additional pin functions: https://pinout.xyz/
Receptacle: 691311500102 Plug: 691351500002
0402
